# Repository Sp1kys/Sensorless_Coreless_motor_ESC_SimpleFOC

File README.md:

# SimpleFOC_Sensorless_Coreless_motor_ESC
 Hardware and software for Custom ESC for Coreless motors

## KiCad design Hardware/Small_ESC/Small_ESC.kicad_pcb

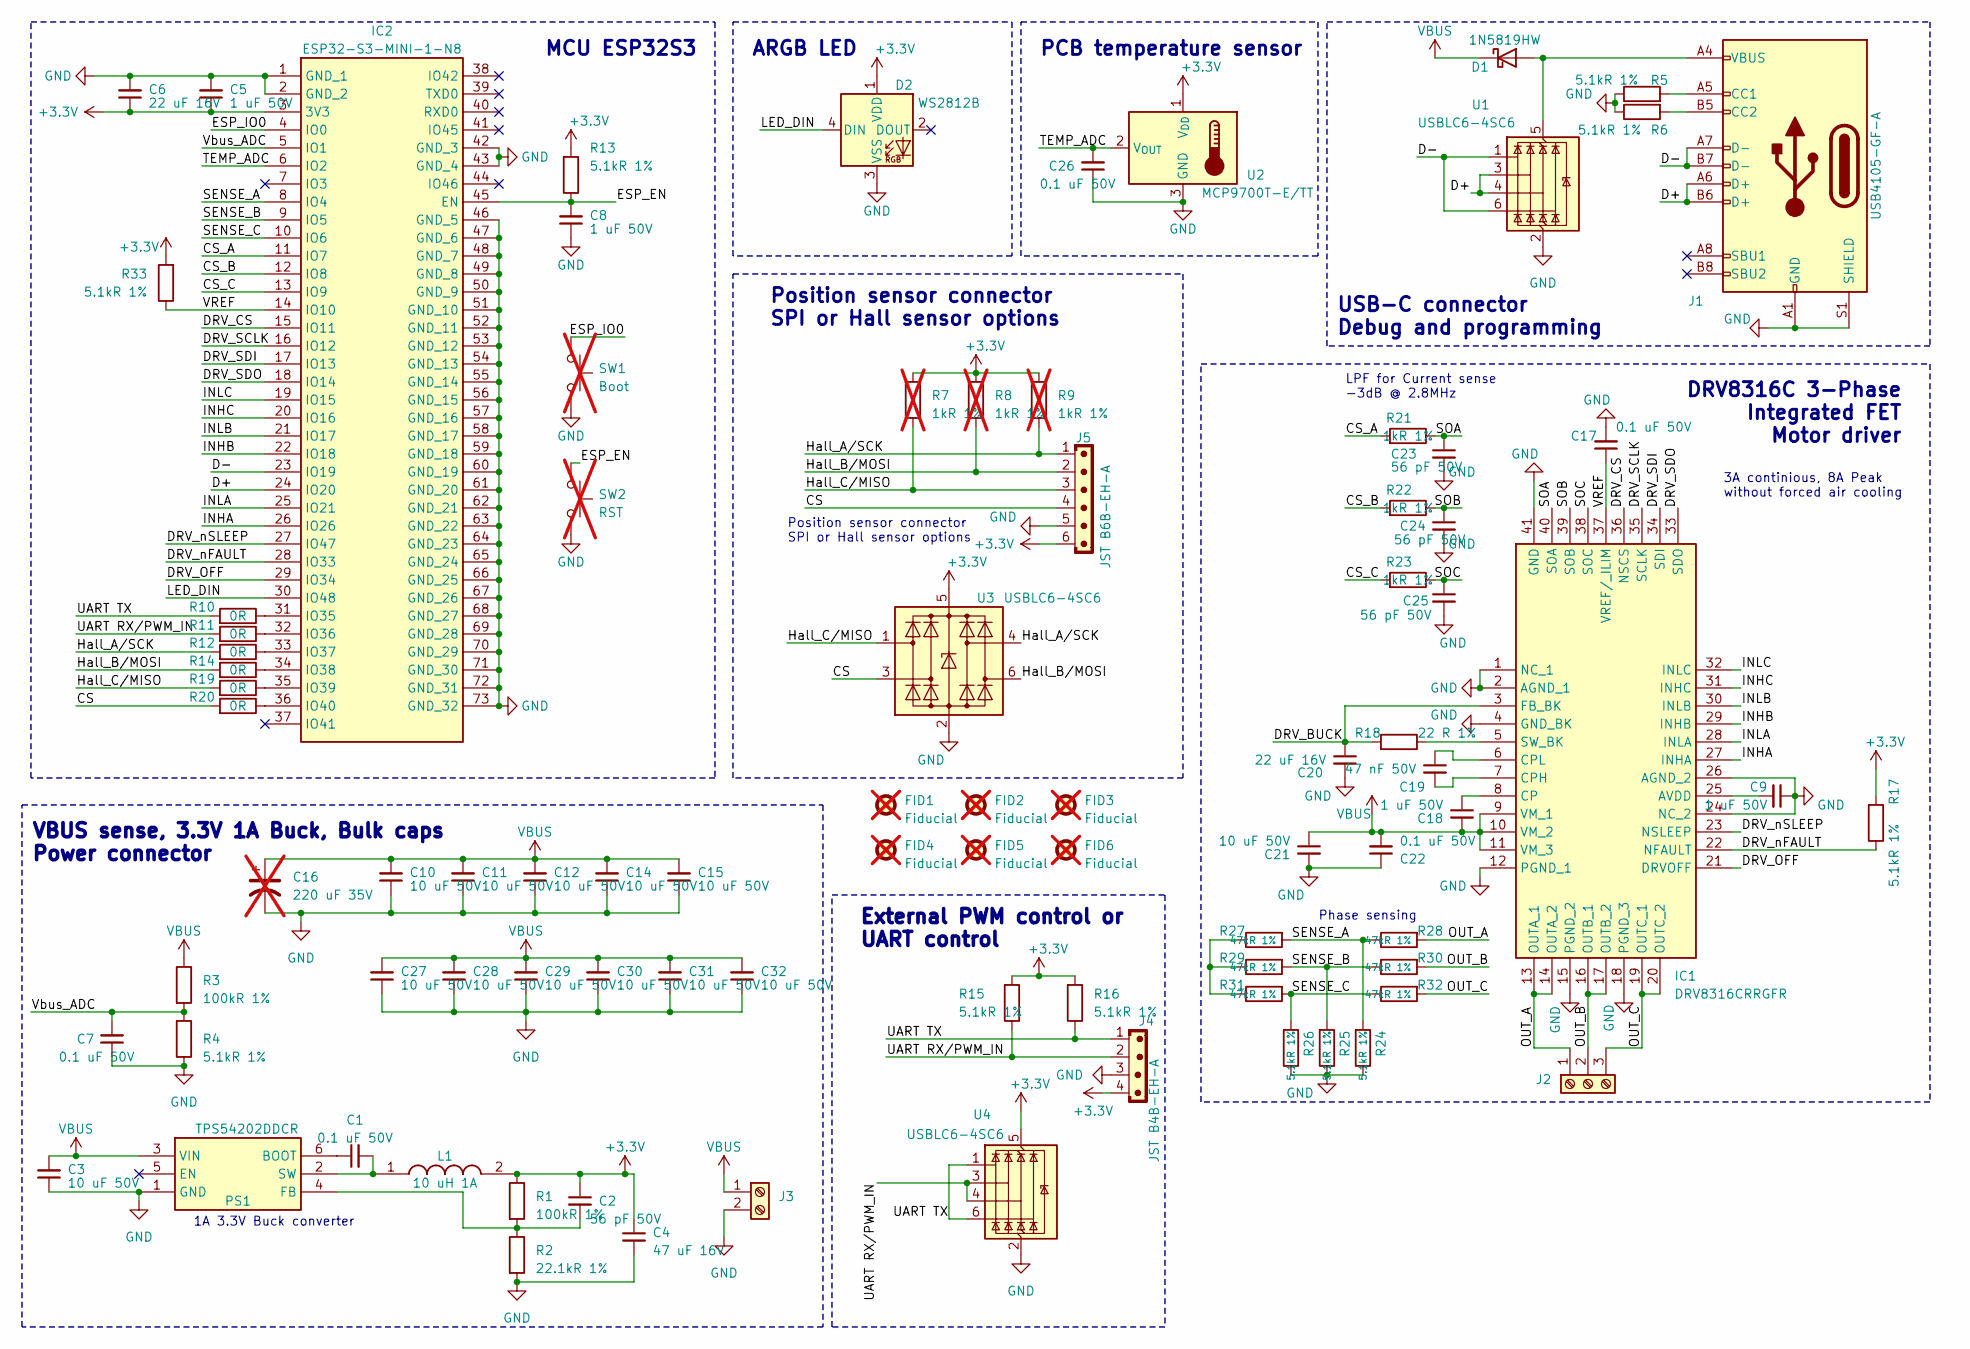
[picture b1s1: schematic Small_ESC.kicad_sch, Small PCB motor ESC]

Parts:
C1, C7, C17, C22, C26: 0.1 uF 50V; C_0402_1005Metric; Manufacturer_Part_Number GCM155R71H104KE02J
C2, C23, C24, C25: 56 pF 50V; C_0402_1005Metric; Manufacturer_Part_Number GCM1555C1H560JA16D
C3, C10, C11, C12, C14, C15, C21, C27, C28, C29, C30, C31, C32: 10 uF 50V; C_0805_2012Metric; Manufacturer_Part_Number GRM21BR61H106KE43L
C4: 47 uF 16V; C_1210_3225Metric; Manufacturer_Part_Number CL32A476KOJNNNE
C5, C8, C9, C18: 1 uF 50V; C_0603_1608Metric; Manufacturer_Part_Number CL10A105KB8NNNC
C6, C20: 22 uF 16V; C_0805_2012Metric; Manufacturer_Part_Number CL21A226MOCLRNC
C16: 220 uF 35V; C_Rect_L7.0mm_W3.5mm_P5.00mm; not fitted
C19: 47 nF 50V; C_0402_1005Metric; Manufacturer_Part_Number GRM155R71H473KE14D
D1: 1N5819HW; D_SOD-123; Manufacturer_Part_Number 1N5819HW-7-F
D2: WS2812B; LED_WS2812B_PLCC4_5.0x5.0mm_P3.2mm; Manufacturer_Part_Number WS2812B-B/T
FID1, FID2, FID3, FID4, FID5, FID6: Fiducial; Fiducial_0.75mm_Mask1.5mm; not fitted
IC1: DRV8316CRRGFR; QFN50P500X700X100-41N-D; Mouser Part Number 595-DRV8316CRRGFR
IC2: ESP32-S3-MINI-1-N8; ESP32S3MINI1N8; Mouser Part Number 356-ESP32-S3-MINI1N8
J1: USB4105-GF-A; USB_C_Receptacle_GCT_USB4105-xx-A_16P_TopMnt_Horizontal; Manufacturer_Part_Number USB4105-GF-A
J2: PT-1,5-3-3.5-H; TerminalBlock_Phoenix_PT-1,5-3-3.5-H_1x03_P3.50mm_Horizontal; Manufacturer_Part_Number 1984620
J3: PT-1,5-2-3.5-H; TerminalBlock_Phoenix_PT-1,5-2-3.5-H_1x02_P3.50mm_Horizontal; Manufacturer_Part_Number 1984617
J4: JST B4B-EH-A; JST_EH_B4B-EH-A_1x04_P2.50mm_Vertical; Manufacturer_Part_Number B4B-EH-A
J5: JST B6B-EH-A; JST_EH_B6B-EH-A_1x06_P2.50mm_Vertical; Manufacturer_Part_Number B6B-EH-A
L1: 10 uH 1A; VLS3015; Mouser Part Number 810-VLS3015CX-100M-H
PS1: TPS54202DDCR; SOT95P280X110-6N; Mouser Part Number 595-TPS54202DDCR
R1, R3: 100kR 1%; R_0402_1005Metric; Manufacturer_Part_Number ERJ-2RKF1003X
R2: 22.1kR 1%; R_0402_1005Metric; Manufacturer_Part_Number ERJ-2RKF2212X
R4, R5, R6, R13, R15, R16, R17, R24, R25, R26, R33: 5.1kR 1%; R_0402_1005Metric; Manufacturer_Part_Number ERJ-2RKF5101X
R7, R8, R9: 1kR 1%; R_0402_1005Metric; Manufacturer_Part_Number ERJ-2RKF1001X; not fitted
R10, R11, R12, R14, R19, R20: 0R; R_0402_1005Metric; Manufacturer_Part_Number RC0402JR-070RL
R18: 22 R 1%; R_0805_2012Metric; Manufacturer_Part_Number ERJ-6ENF22R0V
R21, R22, R23: 1kR 1%; R_0402_1005Metric; Manufacturer_Part_Number ERJ-2RKF1001X
R27, R28, R29, R30, R31, R32: 47kR 1%; R_0402_1005Metric; Manufacturer_Part_Number ERJ-2RKF4702X
SW1: Boot; PinHeader_1x02_P2.54mm_Vertical; not fitted
SW2: RST; PinHeader_1x02_P2.54mm_Vertical; not fitted
U1, U3, U4: USBLC6-4SC6; SOT-23-6; Manufacturer_Part_Number USBLC6-4SC6
U2: MCP9700T-E/TT; SOT-23; Manufacturer_Part_Number MCP9700T-E/TT

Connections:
+3.3V: C2.1, C4.1, C5.1, C6.1, D2.1 (VDD), IC2.3 (3V3), J4.4, J5.6, L1.2, R1.1, R7.1, R8.1, R9.1, R13.2, R15.2, R16.2, R17.2, R33.2, U2.1 (V_{DD}), U3.5 (VBUS), U4.5 (VBUS)
/CS: J5.4, R20.2, U3.3 (I/O2)
/CS_A: IC2.11 (IO7), R21.2
/CS_B: IC2.12 (IO8), R22.2
/CS_C: IC2.13 (IO9), R23.2
/D+: IC2.24 (IO20), J1.A6 (D+), J1.B6 (D+), U1.3 (I/O2), U1.4 (I/O3)
/D-: IC2.23 (IO19), J1.A7 (D-), J1.B7 (D-), U1.1 (I/O1), U1.6 (I/O4)
/DRV_BUCK: C20.1, IC1.3 (FB_BK), R18.2
/DRV_CS: IC1.36 (NSCS), IC2.15 (IO11)
/DRV_OFF: IC1.21 (DRVOFF), IC2.29 (IO34)
/DRV_SCLK: IC1.35 (SCLK), IC2.16 (IO12)
/DRV_SDI: IC1.34 (SDI), IC2.17 (IO13)
/DRV_SDO: IC1.33 (SDO), IC2.18 (IO14)
/DRV_nFAULT: IC1.22 (NFAULT), IC2.28 (IO33), R17.1
/DRV_nSLEEP: IC1.23 (NSLEEP), IC2.27 (IO47)
/ESP_EN: C8.2, IC2.45 (EN), R13.1, SW2.1
/ESP_IO0: IC2.4 (IO0), SW1.1
/Hall_A/SCK: J5.1, R9.2, R12.2, U3.4 (I/O3)
/Hall_B/MOSI: J5.2, R8.2, R14.2, U3.6 (I/O4)
/Hall_C/MISO: J5.3, R7.2, R19.2, U3.1 (I/O1)
/INHA: IC1.27 (INHA), IC2.26 (IO26)
/INHB: IC1.29 (INHB), IC2.22 (IO18)
/INHC: IC1.31 (INHC), IC2.20 (IO16)
/INLA: IC1.28 (INLA), IC2.25 (IO21)
/INLB: IC1.30 (INLB), IC2.21 (IO17)
/INLC: IC1.32 (INLC), IC2.19 (IO15)
/LED_DIN: D2.4 (DIN), IC2.30 (IO48)
/OUT_A: IC1.13 (OUTA_1), IC1.14 (OUTA_2), J2.1, R28.2
/OUT_B: IC1.16 (OUTB_1), IC1.17 (OUTB_2), J2.2, R30.2
/OUT_C: IC1.19 (OUTC_1), IC1.20 (OUTC_2), J2.3, R32.2
/SENSE_A: IC2.8 (IO4), R24.2, R27.2, R28.1
/SENSE_B: IC2.9 (IO5), R25.2, R29.2, R30.1
/SENSE_C: IC2.10 (IO6), R26.2, R31.2, R32.1
/SOA: C23.1, IC1.40 (SOA), R21.1
/SOB: C24.1, IC1.39 (SOB), R22.1
/SOC: C25.1, IC1.38 (SOC), R23.1
/TEMP_ADC: C26.2, IC2.6 (IO2), U2.2 (V_{OUT})
/UART RX/PWM_IN: J4.2, R11.2, R15.1, U4.3 (I/O2), U4.4 (I/O3)
/UART TX: J4.1, R10.2, R16.1, U4.1 (I/O1), U4.6 (I/O4)
/VREF: C17.1, IC1.37 (VREF/_ILIM), IC2.14 (IO10), R33.1
/Vbus_ADC: C7.2, IC2.5 (IO1), R3.2, R4.2
GND: C3.1, C4.2, C5.2, C6.2, C7.1, C8.1, C9.1, C10.1, C11.1, C12.1, C14.1, C15.1, C16.2, C17.2, C20.2, C21.2, C22.1, C23.2, C24.2, C25.2, C26.1, C27.1, C28.1, C29.1, C30.1, C31.1, C32.1, D2.3 (VSS), IC1.1 (NC_1), IC1.2 (AGND_1), IC1.4 (GND_BK), IC1.12 (PGND_1), IC1.15 (PGND_2), IC1.18 (PGND_3), IC1.24 (NC_2), IC1.26 (AGND_2), IC1.41 (GND), IC2.1 (GND_1), IC2.2 (GND_2), IC2.42 (GND_3), IC2.43 (GND_4), IC2.46 (GND_5), IC2.47 (GND_6), IC2.48 (GND_7), IC2.49 (GND_8), IC2.50 (GND_9), IC2.51 (GND_10), IC2.52 (GND_11), IC2.53 (GND_12), IC2.54 (GND_13), IC2.55 (GND_14), IC2.56 (GND_15), IC2.57 (GND_16), IC2.58 (GND_17), IC2.59 (GND_18), IC2.60 (GND_19), IC2.61 (GND_20), IC2.62 (GND_21), IC2.63 (GND_22), IC2.64 (GND_23), IC2.65 (GND_24), IC2.66 (GND_25), IC2.67 (GND_26), IC2.68 (GND_27), IC2.69 (GND_28), IC2.70 (GND_29), IC2.71 (GND_30), IC2.72 (GND_31), IC2.73 (GND_32), J1.A1 (GND), J1.A12 (GND), J1.B1 (GND), J1.B12 (GND), J1.S1 (SHIELD), J3.2, J4.3, J5.5, PS1.1 (GND), R2.2, R4.1, R5.1, R6.1, R24.1, R25.1, R26.1, SW1.2, SW2.2, U1.2 (GND), U2.3 (GND), U3.2 (GND), U4.2 (GND)
unnamed: D1.2 (A), J1.A4 (VBUS), J1.A9 (VBUS), J1.B4 (VBUS), J1.B9 (VBUS), U1.5 (VBUS)
unnamed: C9.2, IC1.25 (AVDD)
unnamed: C18.1, IC1.8 (CP)
unnamed: C19.2, IC1.7 (CPH)
unnamed: C19.1, IC1.6 (CPL)
unnamed: IC1.5 (SW_BK), R18.1
unnamed: IC2.31 (IO35), R10.1
unnamed: IC2.32 (IO36), R11.1
unnamed: IC2.33 (IO37), R12.1
unnamed: IC2.34 (IO38), R14.1
unnamed: IC2.35 (IO39), R19.1
unnamed: IC2.36 (IO40), R20.1
unnamed: J1.A5 (CC1), R5.2
unnamed: J1.B5 (CC2), R6.2
unnamed: C1.1, PS1.6 (BOOT)
unnamed: C2.2, PS1.4 (FB), R1.2, R2.1
unnamed: C1.2, L1.1, PS1.2 (SW)
unnamed: R27.1, R29.1, R31.1
VBUS: C3.2, C10.2, C11.2, C12.2, C14.2, C15.2, C16.1, C18.2, C21.1, C22.2, C27.2, C28.2, C29.2, C30.2, C31.2, C32.2, D1.1 (K), IC1.9 (VM_1), IC1.10 (VM_2), IC1.11 (VM_3), J3.1, PS1.3 (VIN), R3.1

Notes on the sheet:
LPF for Current sense -3dB @ 2.8MHz
VBUS sense, 3.3V 1A Buck, Bulk caps Power connector
Position sensor connector SPI or Hall sensor options
ARGB LED
External PWM control or UART control
DRV8316C 3-Phase Integrated FET Motor driver
3A continious, 8A Peak without forced air cooling
Phase sensing
PCB temperature sensor
MCU ESP32S3
USB-C connector Debug and programming
1A 3.3V Buck converter

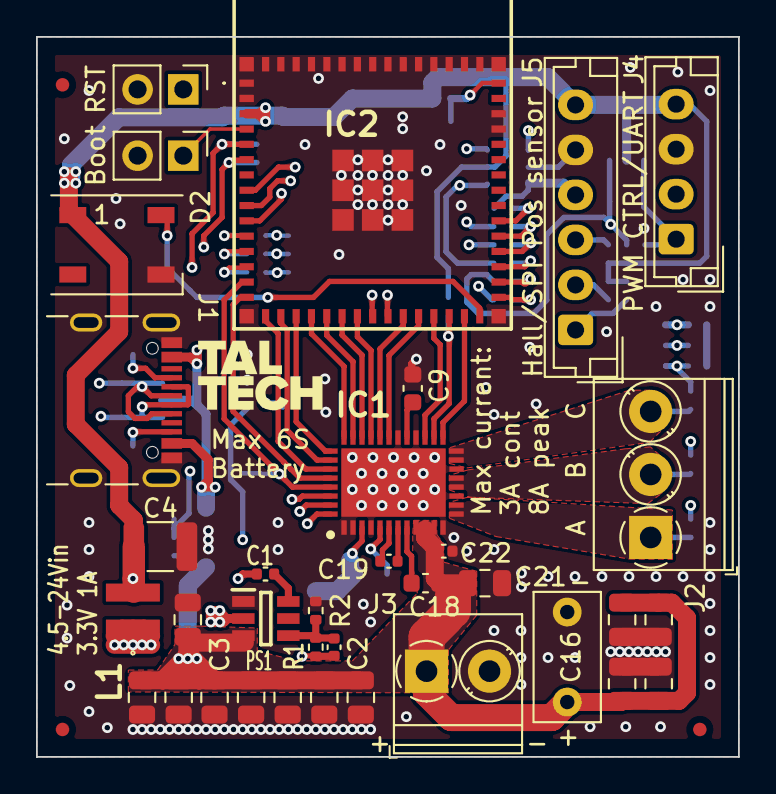
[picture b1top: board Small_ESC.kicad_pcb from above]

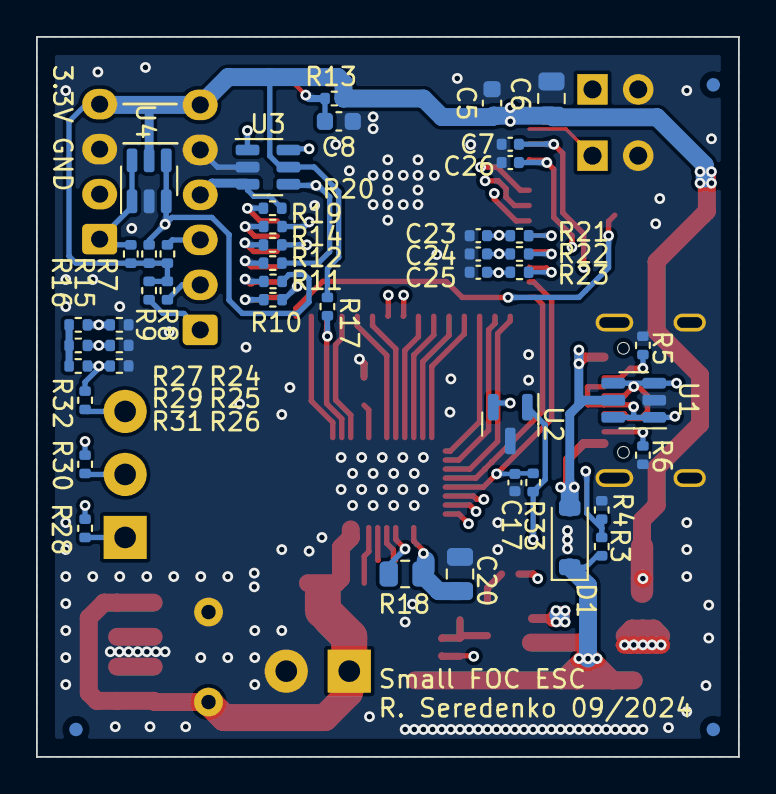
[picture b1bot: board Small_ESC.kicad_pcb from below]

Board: 4 copper layers, 39.0 x 40.0 mm, 87 parts (49 on the bottom side), 61 nets.

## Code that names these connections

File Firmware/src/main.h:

#include "Arduino.h"
#include <SimpleFOC.h>
#include <SimpleFOCDrivers.h>
#include "drivers/drv8316/drv8316.h"
#include <encoders/MXLEMMING_observer/MXLEMMINGObserverSensor.h>
#include <Adafruit_NeoPixel.h>
#include "esp_task_wdt.h"



//Auxiliary pins
#define VBUS_SENSE 1
#define PCB_TEMP 2
#define LED_DIN 48
#define NUM_LEDS 1
#define PIXEL_COUNT 1

//Motor driver IC pins
#define DRV8316_EN 47
#define DRV8316_CS 11
#define nFAULT 33
#define DRV_OFF 34
#define INHA 26
#define INLA 21
#define INHB 18
#define INLB 17
#define INHC 16
#define INLC 15
#define CS_A 7
#define CS_B 8
#define CS_C 9


float target = 0; 				//global variable for target
LowPassFilter LPF_target(2);  	//  the higher the longer new values need to take effect

float R3 = 100; //kOhm
float R4 = 5.1; //kOhm
float velocity_avg, Iq_avg, Id_avg, Vq_avg, Vd_avg, Vin_avg, Iin_avg, temp_avg = 0;

unsigned long timer_start, timer_start_2, count_timer = millis();
unsigned long loops = 0;

Adafruit_NeoPixel strip(PIXEL_COUNT, LED_DIN, NEO_GRB + NEO_KHZ800);

//Different motor presets
//BLDCMotor motor = BLDCMotor(6,0.30625,4000,6.83*1e-6);    //12.7 uH for tiny motor 4300 kV
//BLDCMotor motor = BLDCMotor(11,0.05125,690,4.56*1e-6);    //6.1 uH for large motor 690 kV
//BLDCMotor motor = BLDCMotor(4,0.1375,1100,19.45*1e-6);    //Plastic motor 957 kV
//BLDCMotor motor = BLDCMotor(7,0.01,3500,0.45*1e-6);       //Orange motor 2700 kV?
//BLDCMotor motor = BLDCMotor(4,0.525,1000,3.84*1e-7);      //PCB motor 
BLDCMotor motor = BLDCMotor(1,7,250,3.02*1e-4);             //Experimental Coreless motor 
//BLDCMotor motor = BLDCMotor(6,0.1,12000,0.82*1e-6);       //7300 kV

DRV8316_CSAGain CS_Gain = Gain_0V3;     //Single variable for all Current sense gain
unsigned int CS_Gain_mV = 300;          //150 * 2^(CS_Gain); //Needed for Low Side Current Sense 


MXLEMMINGObserverSensor sensor = MXLEMMINGObserverSensor(motor);
DRV8316Driver6PWM driver = DRV8316Driver6PWM(INHA,INLA,INHB,INLB,INHC,INLC,DRV8316_CS,false);   //Use the right pins for your setup!
LowsideCurrentSense current_sense = LowsideCurrentSense(CS_Gain_mV,CS_A,CS_B,CS_C);             //Default gain is 0.15V/A

TaskHandle_t FOC_TASK;

// commander interface
Commander command = Commander(Serial);
void onMotor(char* cmd){ command.motor(&motor, cmd); }
void doTarget(char* cmd) { command.scalar(&target, cmd); }
void doFW(char* cmd) { command.scalar(&motor.current_sp_field_weakening, cmd); }
void doFL(char* cmd) { command.scalar(&sensor.flux_linkage, cmd); }

void InnerFOCTask( void * parameter );

//Function to read status registers of DRV8316C
void printDRV8316Status() {
	DRV8316Status status = driver.getStatus();
	Serial.println("DRV8316 Status:");
	Serial.print("Fault: ");
	Serial.println(status.isFault());
	Serial.print("Buck Error: ");
	Serial.print(status.isBuckError());
	Serial.print("  Undervoltage: ");
	Serial.print(status.isBuckUnderVoltage());
	Serial.print("  OverCurrent: ");
	Serial.println(status.isBuckOverCurrent());
	Serial.print("Charge Pump UnderVoltage: ");
	Serial.println(status.isChargePumpUnderVoltage());
	Serial.print("OTP Error: ");
	Serial.println(status.isOneTimeProgrammingError());
	Serial.print("OverCurrent: ");
	Serial.print(status.isOverCurrent());
	Serial.print("  Ah: ");
	Serial.print(status.isOverCurrent_Ah());
	Serial.print("  Al: ");
	Serial.print(status.isOverCurrent_Al());
	Serial.print("  Bh: ");
	Serial.print(status.isOverCurrent_Bh());
	Serial.print("  Bl: ");
	Serial.print(status.isOverCurrent_Bl());
	Serial.print("  Ch: ");
	Serial.print(status.isOverCurrent_Ch());
	Serial.print("  Cl: ");
	Serial.println(status.isOverCurrent_Cl());
	Serial.print("OverTemperature: ");
	Serial.print(status.isOverTemperature());
	Serial.print("  Shutdown: ");
	Serial.print(status.isOverTemperatureShutdown());
	Serial.print("  Warning: ");
	Serial.println(status.isOverTemperatureWarning());
	Serial.print("OverVoltage: ");
	Serial.println(status.isOverVoltage());
	Serial.print("PowerOnReset: ");
	Serial.println(status.isPowerOnReset());
	Serial.print("SPI Error: ");
	Serial.print(status.isSPIError());
	Serial.print("  Address: ");
	Serial.print(status.isSPIAddressError());
	Serial.print("  Clock: ");
	Serial.print(status.isSPIClockFramingError());
	Serial.print("  Parity: ");
	Serial.println(status.isSPIParityError());
	if (status.isFault())
		driver.clearFault();
	delayMicroseconds(1); // ensure 400ns delay
	DRV8316_PWMMode val = driver.getPWMMode();
	Serial.print("PWM Mode: ");
	Serial.println(val);
	delayMicroseconds(1); // ensure 400ns delay
	bool lock = driver.isRegistersLocked();
	Serial.print("Lock: ");
	Serial.println(lock);
}

// Rainbow cycle for the onboard LED, used to signal that ESC has started up
void rainbow(int wait) {
  for(long firstPixelHue = 0; firstPixelHue < 3*65536; firstPixelHue += 256) {
    for(int i=0; i<strip.numPixels(); i++) { // For each pixel in strip...

      int pixelHue = firstPixelHue + (i * 65536L / strip.numPixels());
      strip.setPixelColor(i, strip.gamma32(strip.ColorHSV(pixelHue,255,100)));
    }
    strip.show(); // Update strip with new contents
    delay(wait);  // Pause for a moment
  }
}

void configDRV8316(DRV8316_CSAGain gain, DRV8316_Slew slew, DRV8316_OCPLevel OCP, DRV8316_OCPMode OCPMode, DRV8316_OCPDeglitch OCPDeglitch){
	driver.setCurrentSenseGain(gain);
	_delay(10);
	while (driver.getCurrentSenseGain() != gain)
	{
		Serial.println("Gain didn't set, trying again!");
		driver.setCurrentSenseGain(gain);//Gain_1V2  Gain_0V6 Gain_0V3 Gain0_15
		_delay(10);
	}

	driver.setSlew(slew);
	_delay(10);
	while (driver.getSlew() != slew)
	{
		Serial.println("Slew didn't set, trying again!");
		driver.setSlew(slew);
		_delay(10);
	}

	driver.setOCPLevel(OCP);
	_delay(10);
	while (driver.getOCPLevel() != OCP)
	{
		Serial.println("OCP didn't set, trying again!");
		driver.setOCPLevel(OCP);
		_delay(10);
	}

	driver.setOCPDeglitchTime(OCPDeglitch);
	_delay(10);
	while (driver.getOCPDeglitchTime() != OCPDeglitch)
	{
		Serial.println("OCPdeglitch didn't set, trying again!");
		driver.setOCPDeglitchTime(OCPDeglitch);
		_delay(10);
	}

	driver.setOCPMode(OCPMode);
	_delay(10);
	while (driver.getOCPMode() != OCPMode)
	{
		Serial.println("OCPMode didn't set, trying again!");
		driver.setOCPMode(OCPMode);
		_delay(10);
	}

}

void onStatus(char* cmd) { printDRV8316Status(); }

void clearFaultDriver(char* cmd) { 
	driver.clearFault(); 
	digitalWrite(DRV8316_EN, LOW); // Disable Driver
	_delay(100);
	digitalWrite(DRV8316_EN, HIGH); // Enable Driver
	configDRV8316(CS_Gain, Slew_200Vus, Curr_24A, NoAction, Deglitch_1us6);
}

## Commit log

2024-11-15 avg Parameter reporting + remove unused code
2024-12-08 Fix average value reporting and experimental motor resistance
2024-12-08 PCB and SimpleFOC studio
2025-01-05 MCU Firmware to separate folder
2025-01-05 Library with fixes
2025-01-05 some fixes
2025-01-05 Gitignore fix
2025-01-06 Header file + comments in main
2025-01-06 Gitignore
